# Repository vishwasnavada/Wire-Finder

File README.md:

# Wire-Finder
Wire tracing circuit which can trace wires inside walls 
This is PCB design for simple circuit which can be used for tracing wires inside walls

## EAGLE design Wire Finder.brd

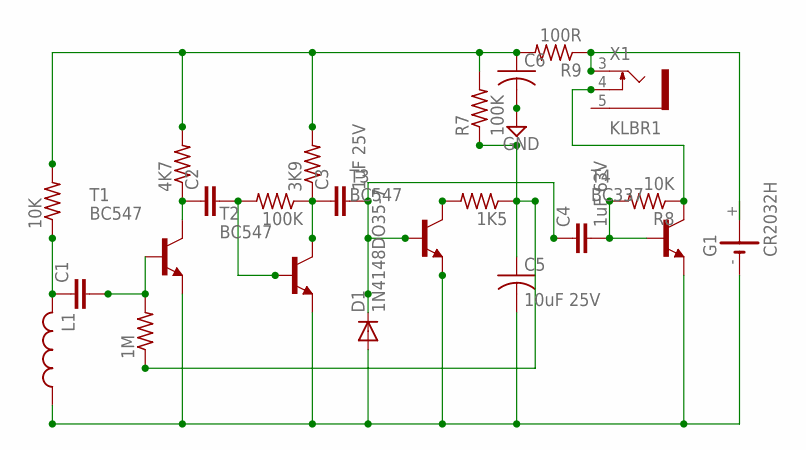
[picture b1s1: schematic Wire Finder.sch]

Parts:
1K5, 1M, 3K9, 4K7, 10K, 100K: R-US_0204/7; 0204/7
C1, C2: C2.5/2; C2.5-2
C3: 1uF 25V; C2.5-2
C4: 1uF 63V; C2.5-2
C5: 10uF 25V; C025-024X044
C6: C-US025-024X044; C025-024X044
D1: 1N4148DO35-7; DO35-7
G1: CR2032H
L1: L-USIR-2; IR-2
R7: 100K; 0204/7
R8: 10K; 0204/7
R9: 100R; 0204/7
T1, T2, T3: BC547; TO92
T4: BC337; TO92
X1: KLBR1

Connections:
GND: C6.2
unnamed: 4K7.1, C2.1, T1.3 (C)
unnamed: 3K9.1, 100K.1, C3.1, T2.3 (C)
unnamed: C3.2, C4.1, D1.C, T3.2 (B)
unnamed: R8.1, T4.3 (C), X1.4
unnamed: 10K.1, C1.1, L1.2
unnamed: 100K.2, C2.2, T2.2 (B)
unnamed: 1M.2, C1.2, T1.2 (B)
unnamed: 1K5.1, 1M.1, C5.1, R7.1
unnamed: G1.+, G1.+@1 (+), R9.1, X1.3
unnamed: 1K5.2, T3.3 (C)
unnamed: C4.2, R8.2, T4.2 (B)
unnamed: C5.2, D1.A, G1.-, L1.1, T1.1 (E), T2.1 (E), T3.1 (E), T4.1 (E)
unnamed: 3K9.2, 4K7.2, 10K.2, C6.1, R7.2, R9.2

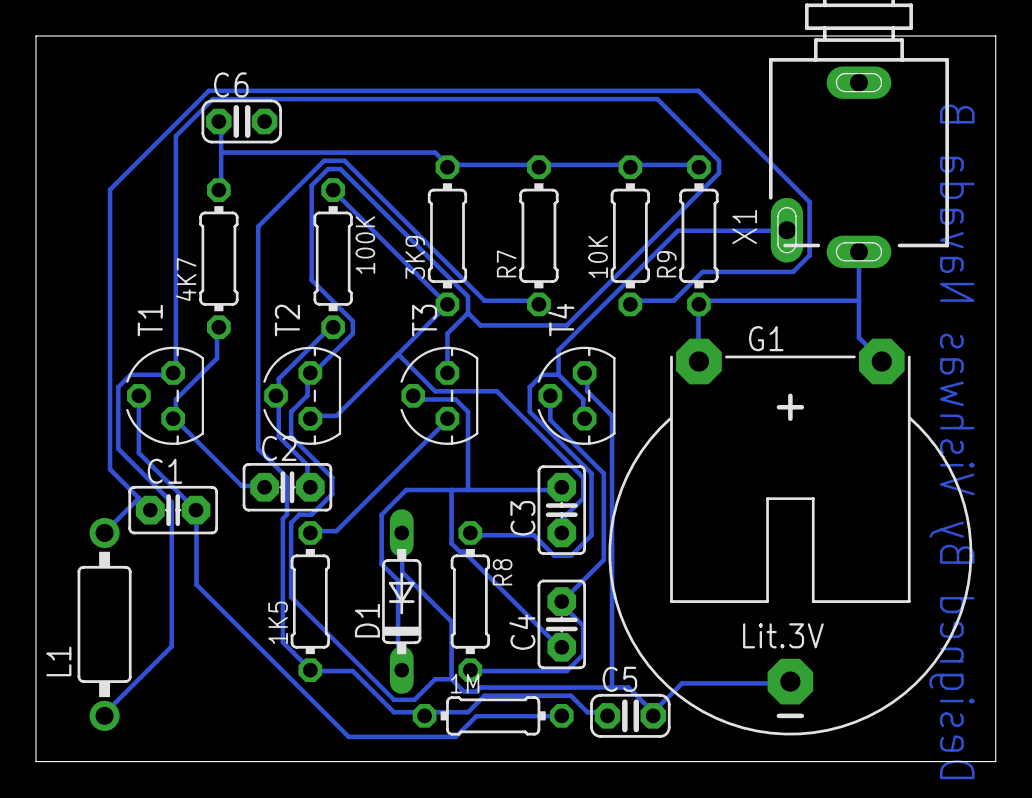
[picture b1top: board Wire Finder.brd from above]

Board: 2 copper layers, 53.3 x 40.3 mm, 23 parts (0 on the bottom side), 13 nets.
